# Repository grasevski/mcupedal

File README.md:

# mcupedal
Guitar effects pedal using attiny85

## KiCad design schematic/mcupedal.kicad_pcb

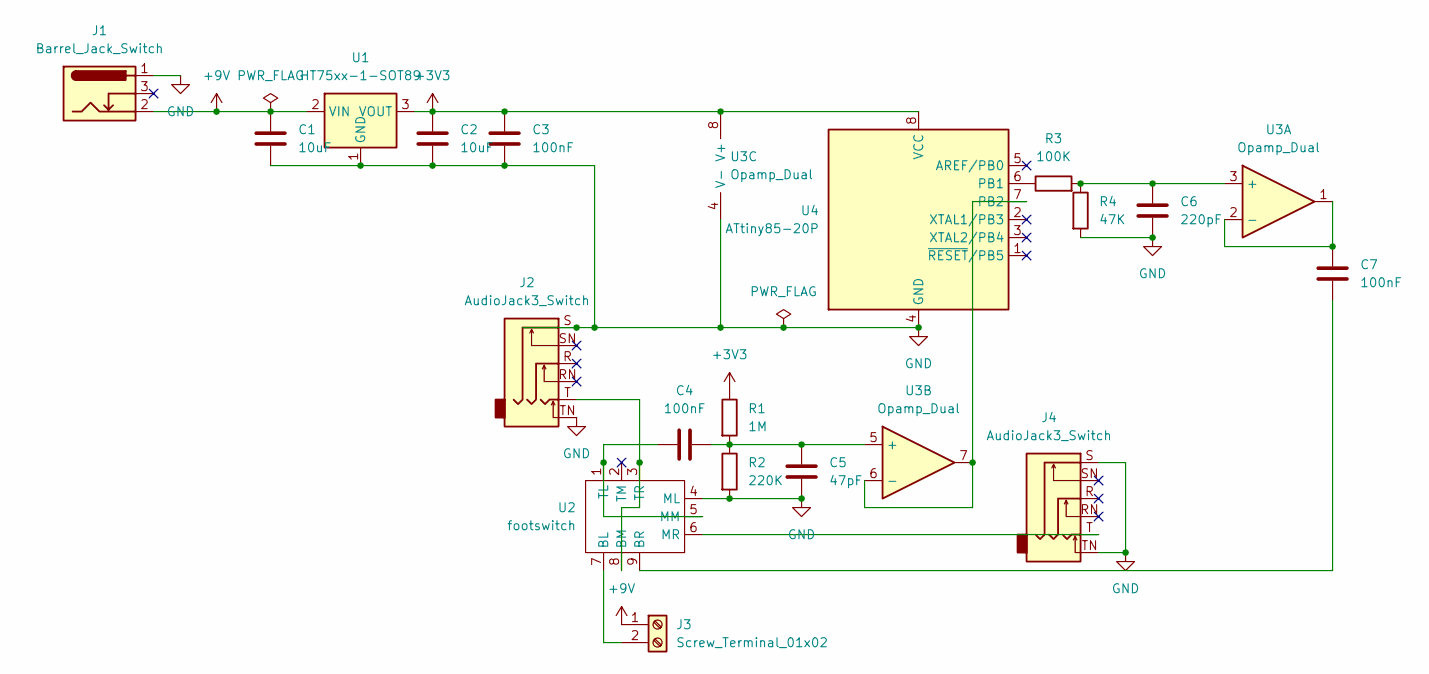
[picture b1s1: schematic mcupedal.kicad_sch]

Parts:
C1, C2: 10uF; C_1206_3216Metric
C3, C4, C7: 100nF; C_1206_3216Metric
C5: 47pF; C_1206_3216Metric
C6: 220pF; C_1206_3216Metric
J1: Barrel_Jack_Switch; BarrelJack_Wuerth_6941xx301002
J2, J4: AudioJack3_Switch; Jack_6.35mm_Neutrik_NMJ6HCD2_Horizontal
J3: Screw_Terminal_01x02; TerminalBlock_Phoenix_MPT-0,5-2-2.54_1x02_P2.54mm_Horizontal
R1: 1M; R_1206_3216Metric
R2: 220K; R_1206_3216Metric
R3: 100K; R_1206_3216Metric
R4: 47K; R_1206_3216Metric
U1: HT75xx-1-SOT89; SOT-89-3
U2: footswitch
U3: Opamp_Dual; DIP-8_W7.62mm_Socket
U4: ATtiny85-20P; DIP-8_W7.62mm_Socket

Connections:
+3V3: C2.1, C3.1, R1.1, U1.3 (VOUT), U3.8 (V+), U4.8 (VCC)
+9V: C1.1, J1.2, J3.1, U1.2 (VIN)
GND: C1.2, C2.2, C3.2, C5.2, C6.2, J1.1, J2.S, J2.TN, J4.S, J4.TN, R2.2, R4.2, U1.1 (GND), U2.4 (ML), U3.4 (V-), U4.4 (GND)
unnamed: C4.1, U2.1 (TL), U2.5 (MM)
unnamed: C4.2, C5.1, R1.2, R2.1, U3.5 (+)
unnamed: C6.1, R3.2, R4.1, U3.3 (+)
unnamed: C7.1, U3.1, U3.2 (-)
unnamed: C7.2, U2.9 (BR)
unnamed: J2.T, U2.3 (TR), U2.8 (BM)
unnamed: J3.2, U2.7 (BL)
unnamed: J4.T, U2.6 (MR)
unnamed: R3.1, U4.6 (PB1)
unnamed: U3.6 (-), U3.7, U4.7 (PB2)

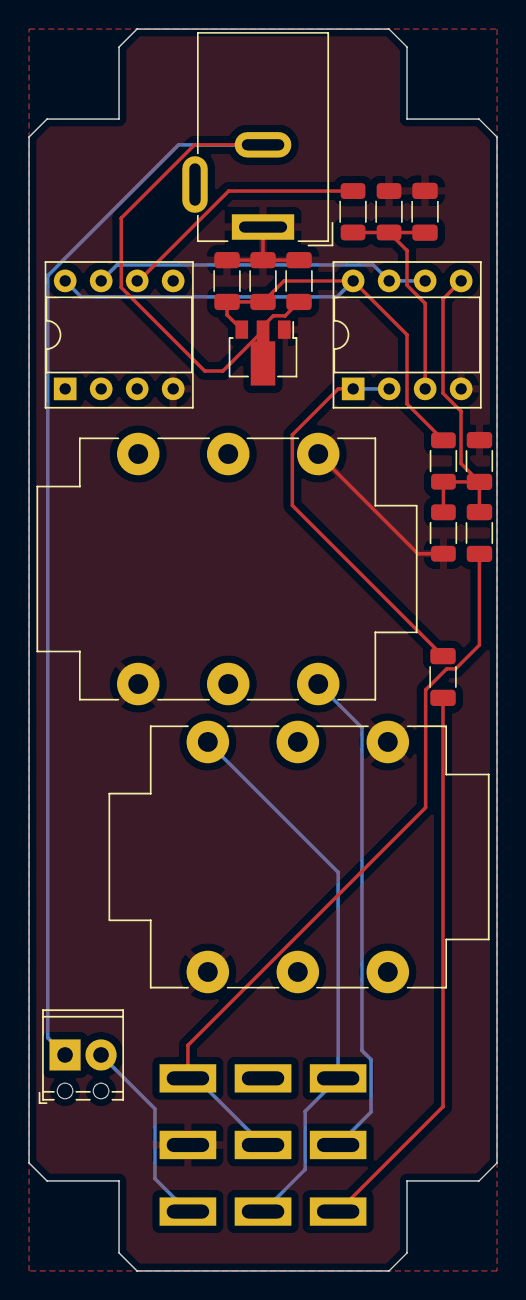
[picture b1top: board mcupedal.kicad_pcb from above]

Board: 2 copper layers, 33.0 x 87.6 mm, 19 parts (0 on the bottom side), 13 nets.

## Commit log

2024-12-19 feat(schematic): first draft
    This includes the schematic and the code of the first draft. It is
    untested.
2024-12-22 chore(refactor): run pwm faster
2024-12-26 chore(init): let the timer start the conversion
2025-01-28 feat(pcb): swap dc pins
2025-02-13 feat(schematic): cleanup
2025-02-14 feat(dsp): overdrive
2025-02-16 feat(dsp): glam metal distortion
2025-04-01 feat(mcupedal): sticking with avr
2025-04-02 chore(tidy): removed unused components
